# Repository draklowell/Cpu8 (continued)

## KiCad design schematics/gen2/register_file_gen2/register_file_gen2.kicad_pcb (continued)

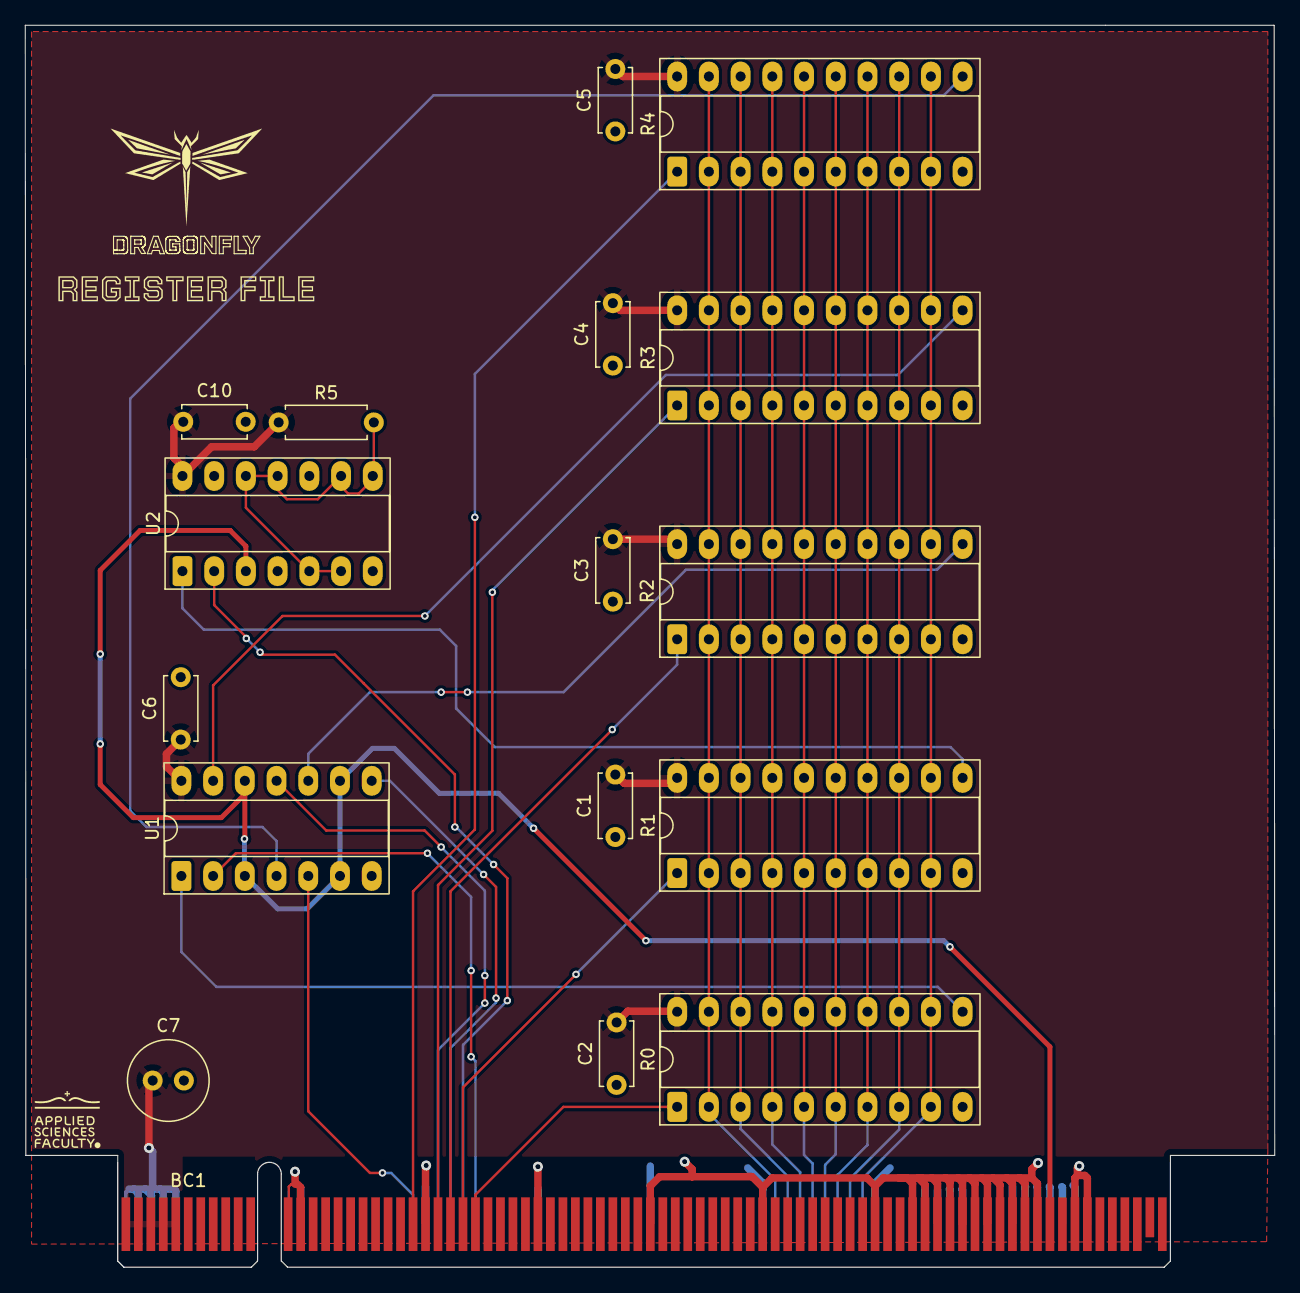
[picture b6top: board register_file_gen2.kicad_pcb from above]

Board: 2 copper layers, 100.0 x 99.5 mm, 18 parts (0 on the bottom side), 27 nets.

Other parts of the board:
kibuzzard-6911B41A: G***; kibuzzard-6911B41A
